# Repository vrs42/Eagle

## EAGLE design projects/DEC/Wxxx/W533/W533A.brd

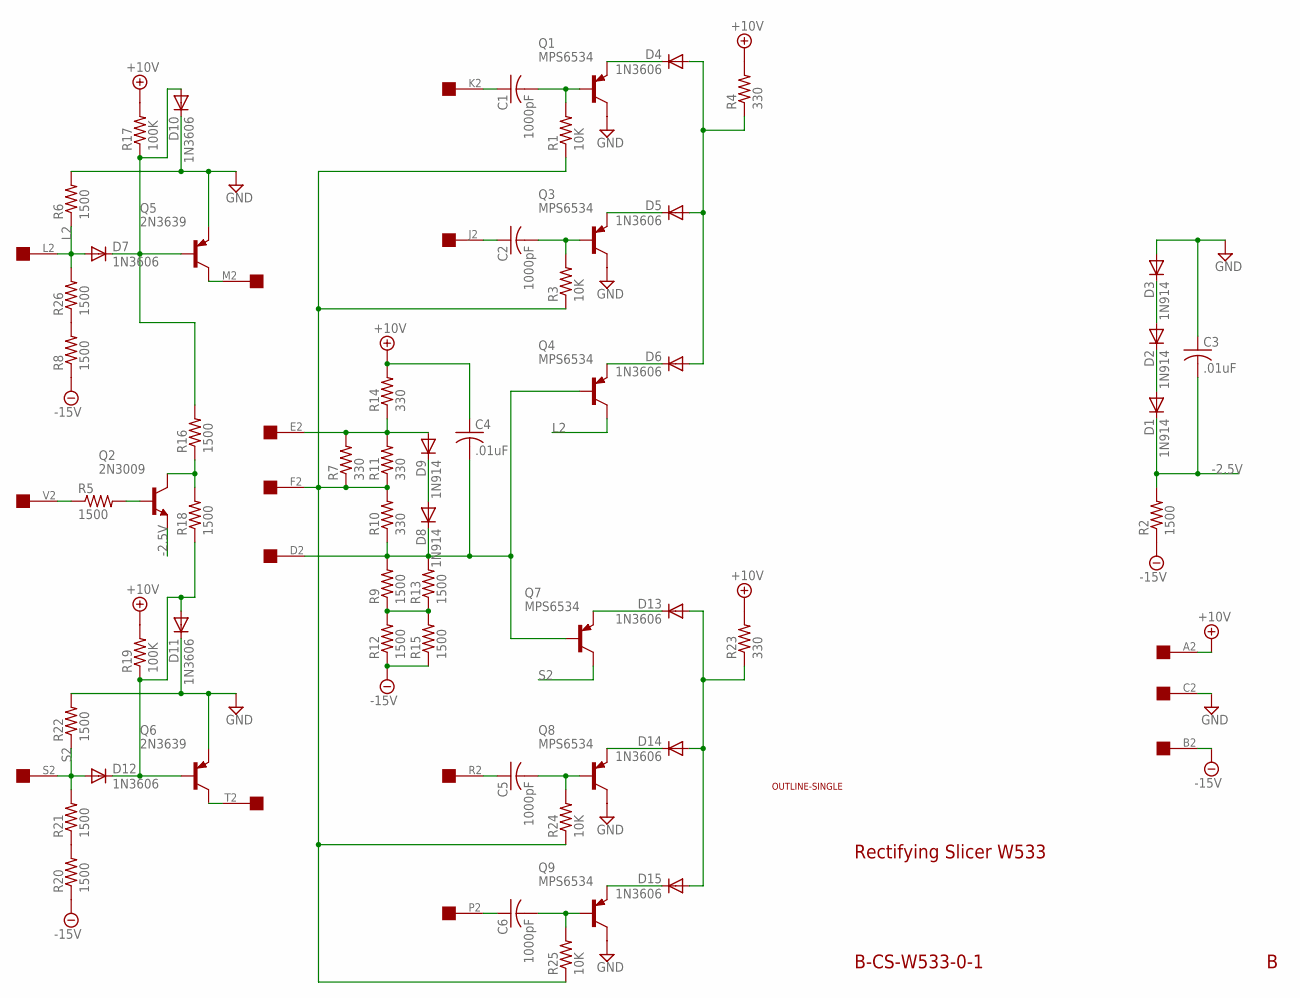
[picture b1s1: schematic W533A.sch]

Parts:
C1, C2, C5, C6: 1000pF; C075-032X103
C3, C4: .01uF; C050-025X075
D1, D2, D3, D8, D9: 1N914; DO35-10
D4, D5, D6, D7, D10, D11, D12, D13, D14, D15: 1N3606; DO35-10
Q1, Q3, Q4, Q7, Q8, Q9: MPS6534; TO39
Q2: 2N3009; TO5
Q5, Q6: 2N3639; TO39
R1, R3, R24, R25: 10K; 0207/10
R2, R5, R6, R8, R9, R12, R13, R15, R16, R18, R20, R21, R22, R26: 1500; 0207/10
R4, R7, R10, R11, R14, R23: 330; 0207/10
R17, R19: 100K; 0207/10
U$1: OUTLINE-SINGLE; SINGLE
U$2: EDGE-1; EDGE-CON1

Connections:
+10V: C4.1, R4.2, R14.2, R17.2, R19.2, R23.2, U$2.A2
-2.5V: C3.2, D1.C, Q2.1 (E), R2.2
-15V: R2.1, R8.1, R12.1, R15.1, R20.1, U$2.B2
GND: C3.1, D3.A, D10.C, D11.C, Q1.3 (C), Q3.3 (C), Q5.1 (E), Q6.1 (E), Q8.3 (C), Q9.3 (C), R6.2, R22.2, U$2.C2
L2: D7.A, Q4.3 (C), R6.1, R26.2, U$2.L2
unnamed: C1.1, U$2.K2
unnamed: R5.1, U$2.V2
unnamed: C1.2, Q1.2 (B), R1.2
unnamed: D4.C, Q1.1 (E)
unnamed: D5.C, Q3.1 (E)
unnamed: C2.1, U$2.J2
unnamed: D14.C, Q8.1 (E)
unnamed: C2.2, Q3.2 (B), R3.2
unnamed: D15.C, Q9.1 (E)
unnamed: Q2.2 (B), R5.2
unnamed: C5.1, U$2.R2
unnamed: Q6.3 (C), U$2.T2
unnamed: C5.2, Q8.2 (B), R24.2
unnamed: Q5.3 (C), U$2.M2
unnamed: R8.2, R26.1
unnamed: C6.1, U$2.P2
unnamed: D13.C, Q7.1 (E)
unnamed: C6.2, Q9.2 (B), R25.2
unnamed: R20.2, R21.1
unnamed: D6.C, Q4.1 (E)
unnamed: D7.C, D10.A, Q5.2 (B), R16.2, R17.1
unnamed: Q2.3 (C), R16.1, R18.2
unnamed: C4.2, D8.C, Q4.2 (B), Q7.2 (B), R9.2, R10.1, R13.2, U$2.D2
unnamed: D11.A, D12.C, Q6.2 (B), R18.1, R19.1
unnamed: R9.1, R12.2, R13.1, R15.2
unnamed: R1.1, R3.1, R7.1, R10.2, R11.1, R24.1, R25.1, U$2.F2
unnamed: D2.A, D3.C
unnamed: D4.A, D5.A, D6.A, R4.1
unnamed: D1.A, D2.C
unnamed: D8.A, D9.C
unnamed: D9.A, R7.2, R11.2, R14.1, U$2.E2
unnamed: D13.A, D14.A, D15.A, R23.1
S2: D12.A, Q7.3 (C), R21.2, R22.1, U$2.S2

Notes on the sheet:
Rectifying Slicer W533
B-CS-W533-0-1

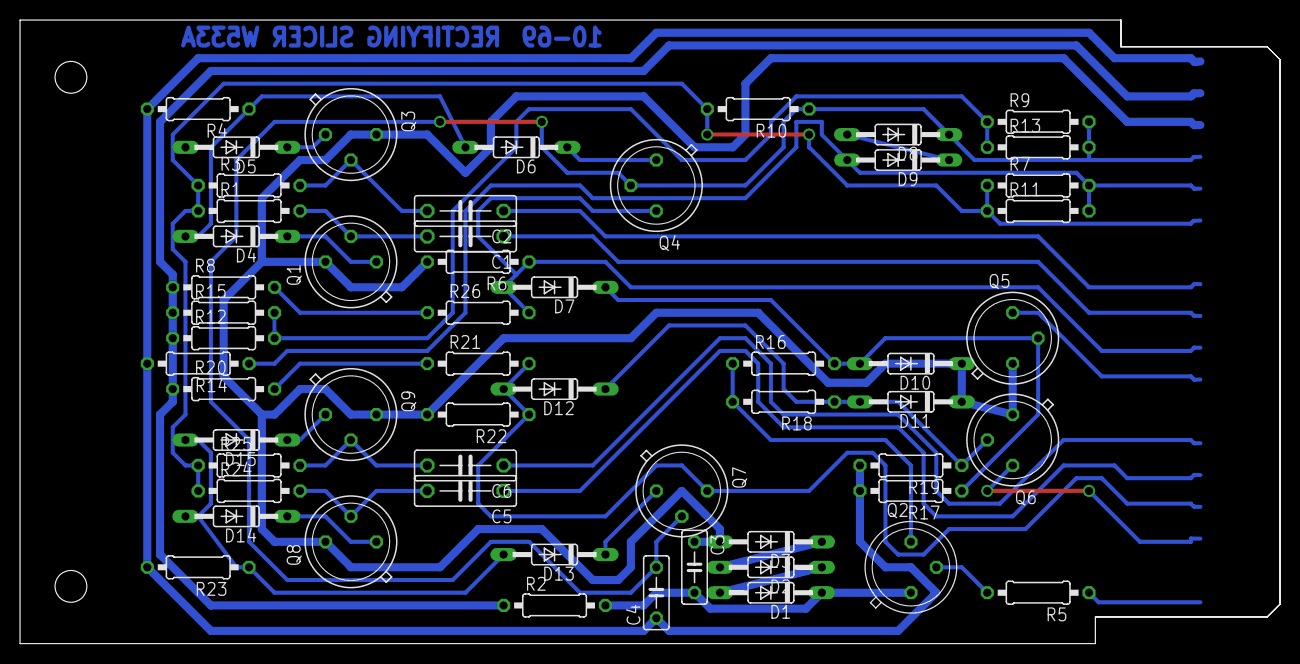
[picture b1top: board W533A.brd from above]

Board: 2 copper layers, 125.7 x 62.2 mm, 58 parts (0 on the bottom side), 38 nets.

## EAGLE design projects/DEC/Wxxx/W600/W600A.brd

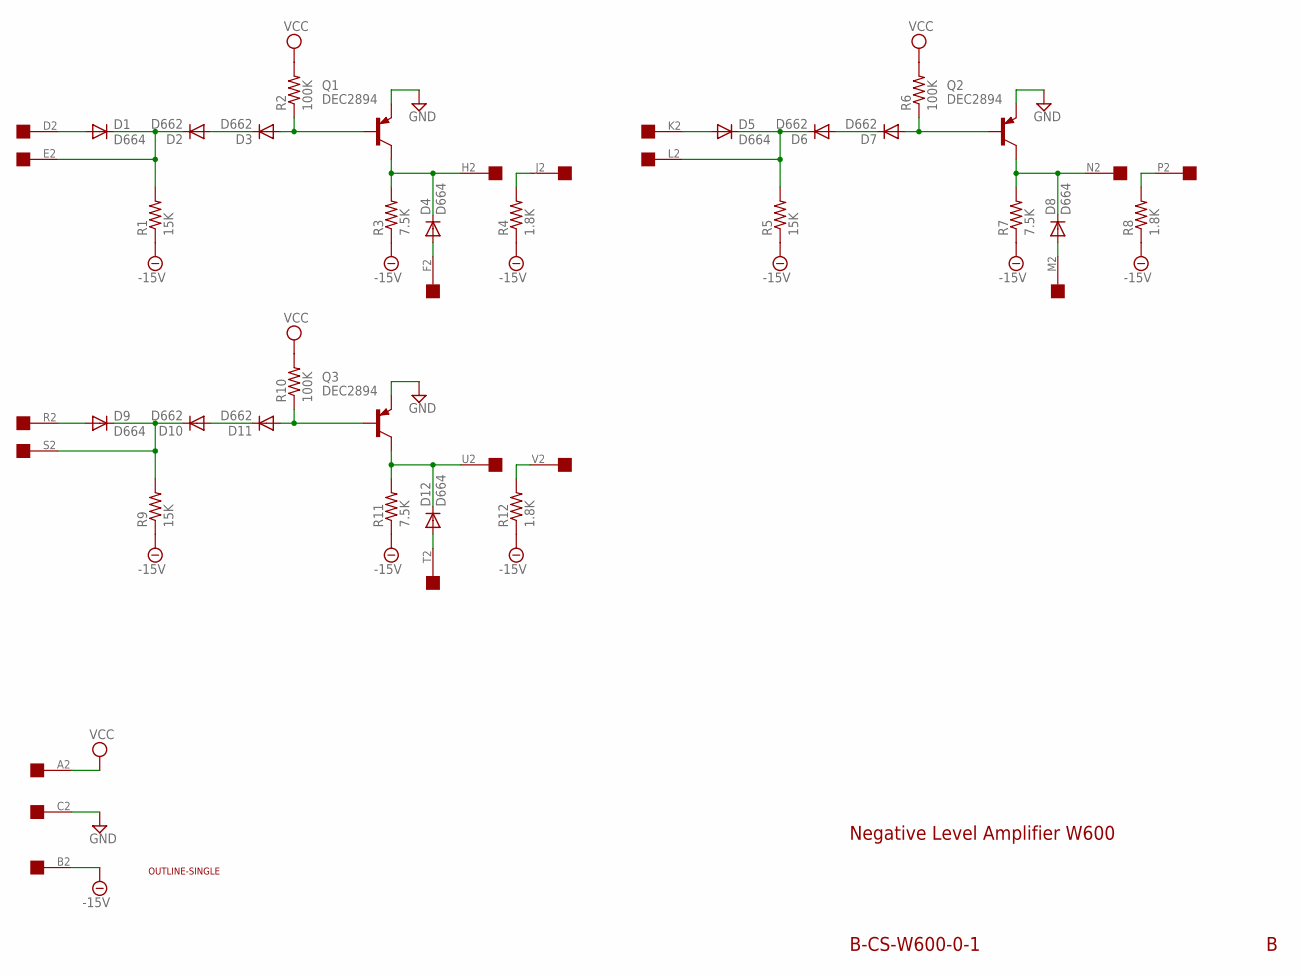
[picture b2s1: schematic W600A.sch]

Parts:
D1, D4, D5, D8, D9, D12: D664; DO35-10
D2, D3, D6, D7, D10, D11: D662; DO35-10
Q1, Q2, Q3: DEC2894; TO5
R1, R5, R9: 15K; 0207/10
R2, R6, R10: 100K; 0207/10
R3, R7, R11: 7.5K; 0207/10
R4, R8, R12: 1.8K; 0207/10
U$1: OUTLINE-SINGLE; SINGLE
U$2: EDGE-1; EDGE-CON1

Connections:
-15V: R1.1, R3.1, R4.1, R5.1, R7.1, R8.1, R9.1, R11.1, R12.1, U$2.B2
GND: Q1.1 (E), Q2.1 (E), Q3.1 (E), U$2.C2
unnamed: D3.A, Q1.2 (B), R2.1
unnamed: D2.A, D3.C
unnamed: D1.C, D2.C, R1.2, U$2.E2
unnamed: D1.A, U$2.D2
unnamed: D4.C, Q1.3 (C), R3.2, U$2.H2
unnamed: R4.2, U$2.J2
unnamed: D7.A, Q2.2 (B), R6.1
unnamed: D6.A, D7.C
unnamed: D5.C, D6.C, R5.2, U$2.L2
unnamed: D5.A, U$2.K2
unnamed: D8.C, Q2.3 (C), R7.2, U$2.N2
unnamed: R8.2, U$2.P2
unnamed: D11.A, Q3.2 (B), R10.1
unnamed: D10.A, D11.C
unnamed: D9.C, D10.C, R9.2, U$2.S2
unnamed: D9.A, U$2.R2
unnamed: D12.C, Q3.3 (C), R11.2, U$2.U2
unnamed: R12.2, U$2.V2
unnamed: D12.A, U$2.T2
unnamed: D4.A, U$2.F2
unnamed: D8.A, U$2.M2
VCC: R2.2, R6.2, R10.2, U$2.A2

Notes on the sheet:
Negative Level Amplifier W600
B-CS-W600-0-1

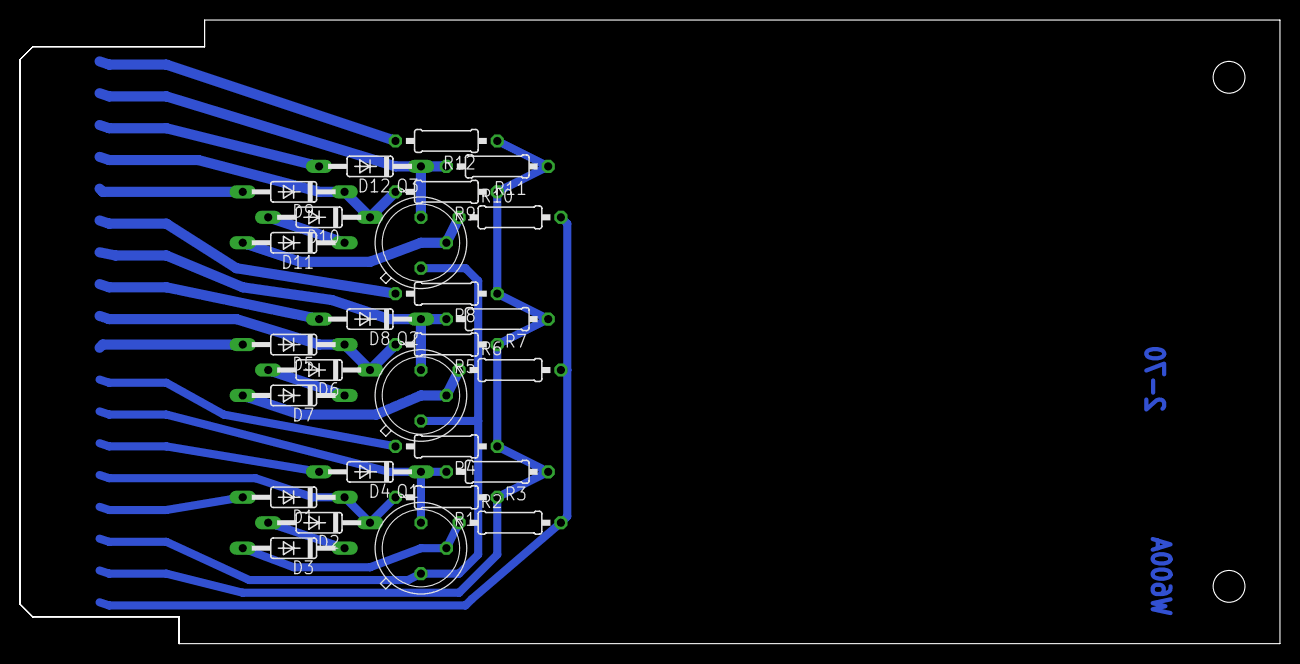
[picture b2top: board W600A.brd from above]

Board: 2 copper layers, 125.7 x 62.2 mm, 29 parts (0 on the bottom side), 24 nets.

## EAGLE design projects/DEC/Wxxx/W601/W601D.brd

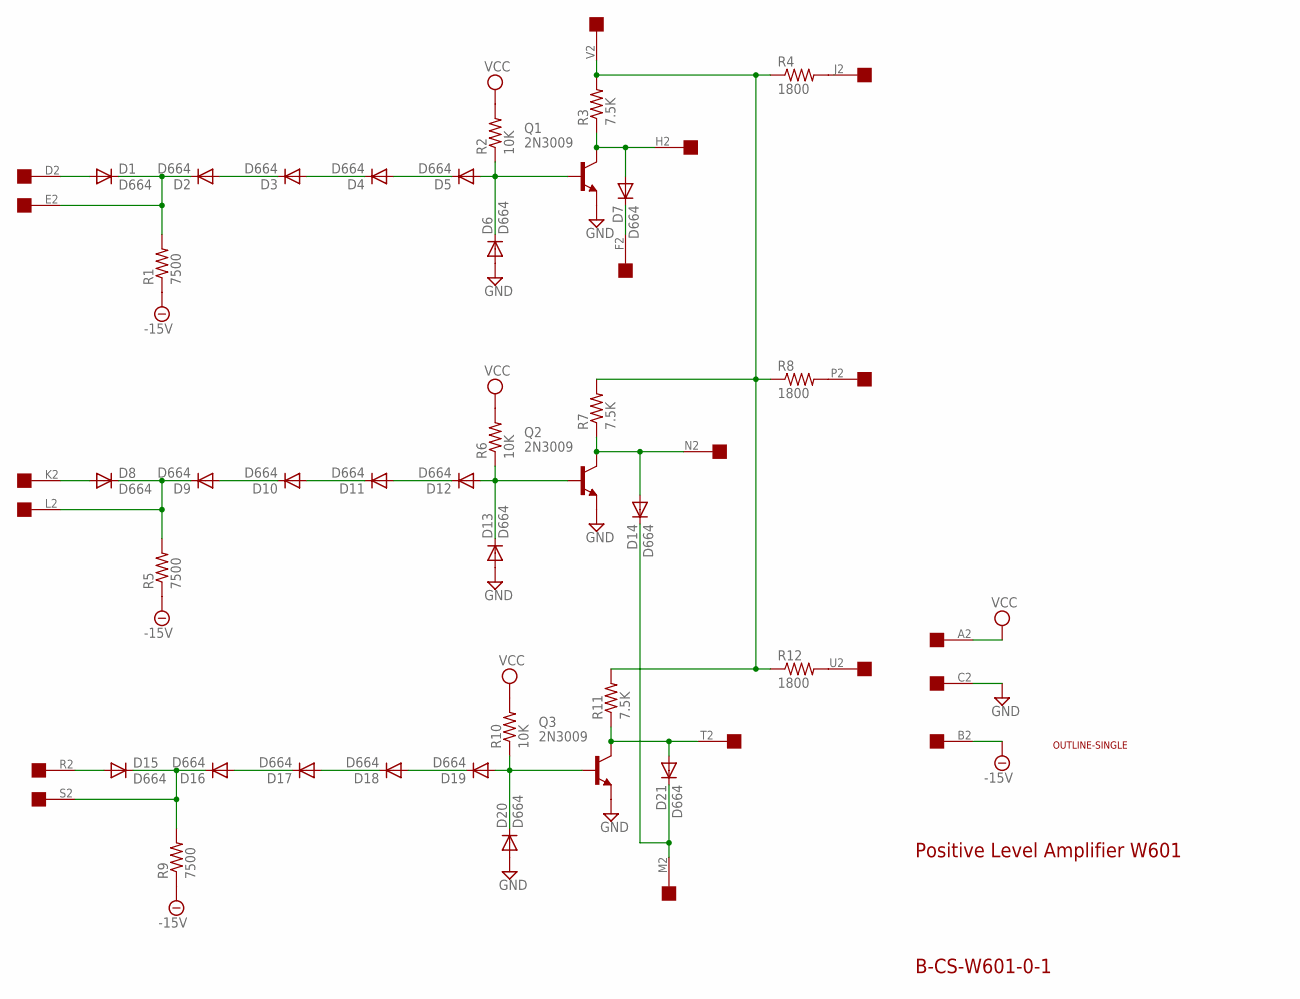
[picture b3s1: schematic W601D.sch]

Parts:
D1, D2, D3, D4, D5, D6, D7, D8, D9, D10, D11, D12, D13, D14, D15, D16, D17, D18, D19, D20, D21: D664; DO35-10
Q1, Q2, Q3: 2N3009; TO5
R1, R5, R9: 7500; 0207/10
R2, R6, R10: 10K; 0207/10
R3, R7, R11: 7.5K; 0207/10
R4, R8, R12: 1800; 0207/10
U$1: OUTLINE-SINGLE; SINGLE
U$2: EDGE-1; EDGE-CON1

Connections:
-15V: R1.1, R5.1, R9.1, U$2.B2
GND: D6.A, D13.A, D20.A, Q1.1 (E), Q2.1 (E), Q3.1 (E), U$2.C2
unnamed: D5.A, D6.C, Q1.2 (B), R2.1
unnamed: D4.A, D5.C
unnamed: D1.C, D2.C, R1.2, U$2.E2
unnamed: D1.A, U$2.D2
unnamed: D7.A, Q1.3 (C), R3.1, U$2.H2
unnamed: R4.2, U$2.J2
unnamed: D12.A, D13.C, Q2.2 (B), R6.1
unnamed: D11.A, D12.C
unnamed: D8.C, D9.C, R5.2, U$2.L2
unnamed: D8.A, U$2.K2
unnamed: D14.C, D21.C, U$2.M2
unnamed: R8.2, U$2.P2
unnamed: D19.A, D20.C, Q3.2 (B), R10.1
unnamed: D18.A, D19.C
unnamed: D15.C, D16.C, R9.2, U$2.S2
unnamed: D15.A, U$2.R2
unnamed: D7.C, U$2.F2
unnamed: R12.2, U$2.U2
unnamed: R3.2, R4.1, R7.2, R8.1, R11.2, R12.1, U$2.V2
unnamed: D16.A, D17.C
unnamed: D17.A, D18.C
unnamed: D9.A, D10.C
unnamed: D10.A, D11.C
unnamed: D2.A, D3.C
unnamed: D14.A, Q2.3 (C), R7.1, U$2.N2
unnamed: D21.A, Q3.3 (C), R11.1, U$2.T2
unnamed: D3.A, D4.C
VCC: R2.2, R6.2, R10.2, U$2.A2

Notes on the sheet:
Positive Level Amplifier W601
B-CS-W601-0-1

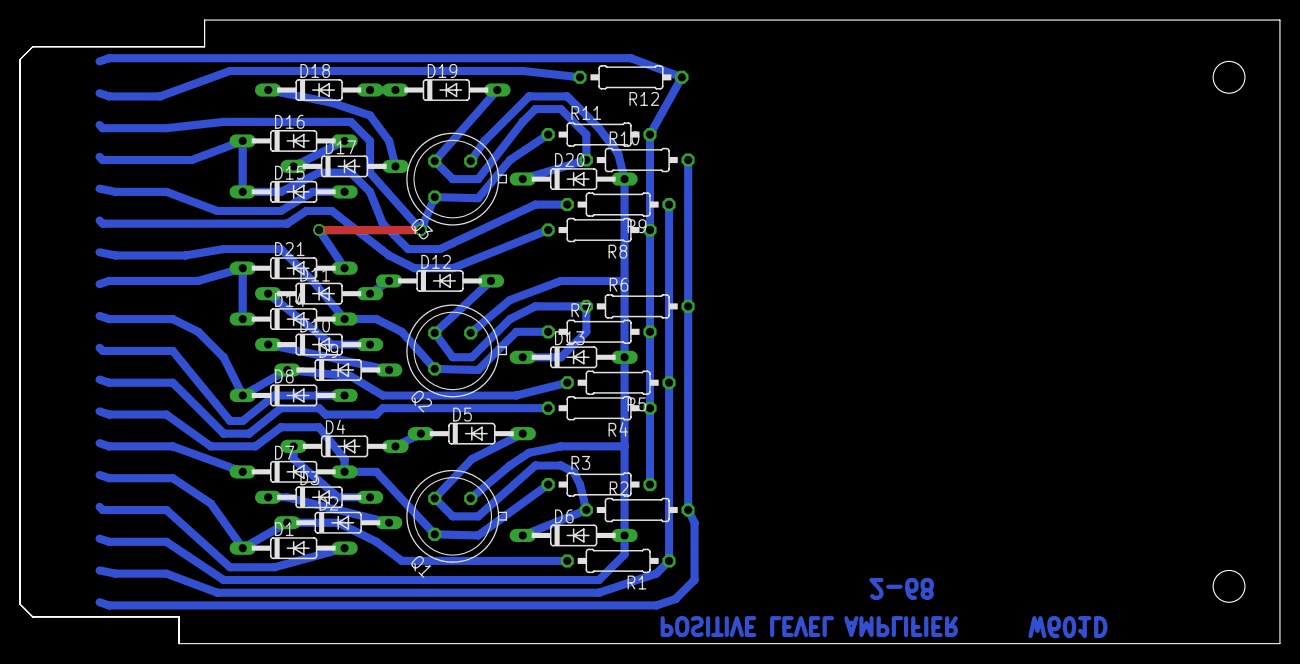
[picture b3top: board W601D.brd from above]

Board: 2 copper layers, 125.7 x 62.2 mm, 38 parts (0 on the bottom side), 30 nets.

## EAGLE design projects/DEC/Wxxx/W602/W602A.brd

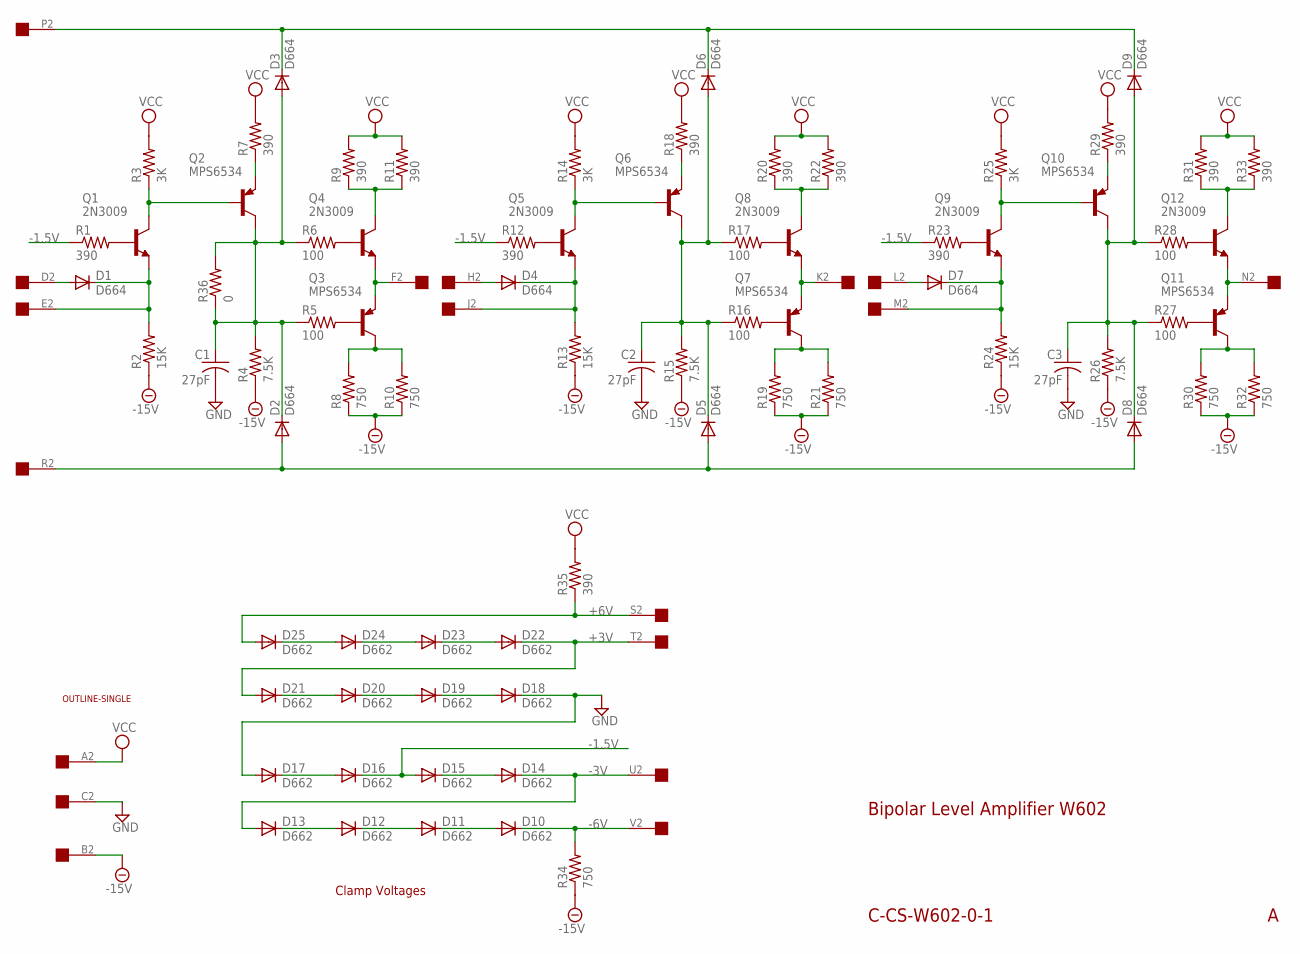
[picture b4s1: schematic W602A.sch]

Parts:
C1, C2, C3: 27pF; C063-025X075
D1, D2, D3, D4, D5, D6, D7, D8, D9: D664; DO35-10
D10, D11, D12, D13, D14, D15, D16, D17, D18, D19, D20, D21, D22, D23, D24, D25: D662; DO35-10
Q1, Q4, Q5, Q8, Q9, Q12: 2N3009; TO5
Q2, Q3, Q6, Q7, Q10, Q11: MPS6534; TO5
R1, R7, R9, R11, R12, R18, R20, R22, R23, R29, R31, R33, R35: 390; 0207/10
R2, R13, R24: 15K; 0207/10
R3, R14, R25: 3K; 0207/10
R4, R15, R26: 7.5K; 0207/10
R5, R6, R16, R17, R27, R28: 100; 0207/10
R8, R10, R19, R21, R30, R32, R34: 750; 0207/10
R36: 0; 0207/10
U$1: OUTLINE-SINGLE; SINGLE
U$2: EDGE-1; EDGE-CON1

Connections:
+3V: D21.A, D22.C, U$2.T2
+6V: D25.A, R35.1, U$2.S2
-1.5V: D15.A, D16.C, R1.1, R12.1, R23.1
-3V: D13.A, D14.C, U$2.U2
-6V: D10.C, R34.2, U$2.V2
-15V: R2.1, R4.1, R8.1, R10.1, R13.1, R15.1, R19.1, R21.1, R24.1, R26.1, R30.1, R32.1, R34.1, U$2.B2
GND: C1.2, C2.2, C3.2, D17.A, D18.C, U$2.C2
unnamed: Q1.3 (C), Q2.2 (B), R3.1
unnamed: Q2.1 (E), R7.1
unnamed: C1.1, D2.C, D3.A, Q2.3 (C), R4.2, R5.1, R6.1, R36.1, R36.2
unnamed: Q1.2 (B), R1.2
unnamed: D1.C, Q1.1 (E), R2.2, U$2.E2
unnamed: D1.A, U$2.D2
unnamed: Q3.3 (C), R8.2, R10.2
unnamed: Q3.2 (B), R5.2
unnamed: Q5.3 (C), Q6.2 (B), R14.1
unnamed: Q4.2 (B), R6.2
unnamed: Q3.1 (E), Q4.1 (E), U$2.F2
unnamed: Q4.3 (C), R9.1, R11.1
unnamed: Q6.1 (E), R18.1
unnamed: C2.1, D5.C, D6.A, Q6.3 (C), R15.2, R16.1, R17.1
unnamed: Q5.2 (B), R12.2
unnamed: D4.C, Q5.1 (E), R13.2, U$2.J2
unnamed: D4.A, U$2.H2
unnamed: Q7.3 (C), R19.2, R21.2
unnamed: Q7.2 (B), R16.2
unnamed: Q8.2 (B), R17.2
unnamed: Q7.1 (E), Q8.1 (E), U$2.K2
unnamed: Q8.3 (C), R20.1, R22.1
unnamed: Q9.3 (C), Q10.2 (B), R25.1
unnamed: Q10.1 (E), R29.1
unnamed: C3.1, D8.C, D9.A, Q10.3 (C), R26.2, R27.1, R28.1
unnamed: Q9.2 (B), R23.2
unnamed: D7.C, Q9.1 (E), R24.2, U$2.M2
unnamed: D7.A, U$2.L2
unnamed: Q11.3 (C), R30.2, R32.2
unnamed: Q11.2 (B), R27.2
unnamed: Q12.2 (B), R28.2
unnamed: Q11.1 (E), Q12.1 (E), U$2.N2
unnamed: Q12.3 (C), R31.1, R33.1
unnamed: D2.A, D5.A, D8.A, U$2.R2
unnamed: D3.C, D6.C, D9.C, U$2.P2
unnamed: D10.A, D11.C
unnamed: D11.A, D12.C
unnamed: D12.A, D13.C
unnamed: D14.A, D15.C
unnamed: D16.A, D17.C
unnamed: D18.A, D19.C
unnamed: D19.A, D20.C
unnamed: D20.A, D21.C
unnamed: D22.A, D23.C
unnamed: D23.A, D24.C
unnamed: D24.A, D25.C
VCC: R3.2, R7.2, R9.2, R11.2, R14.2, R18.2, R20.2, R22.2, R25.2, R29.2, R31.2, R33.2, R35.2, U$2.A2

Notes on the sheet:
Clamp Voltages
Bipolar Level Amplifier W602
C-CS-W602-0-1

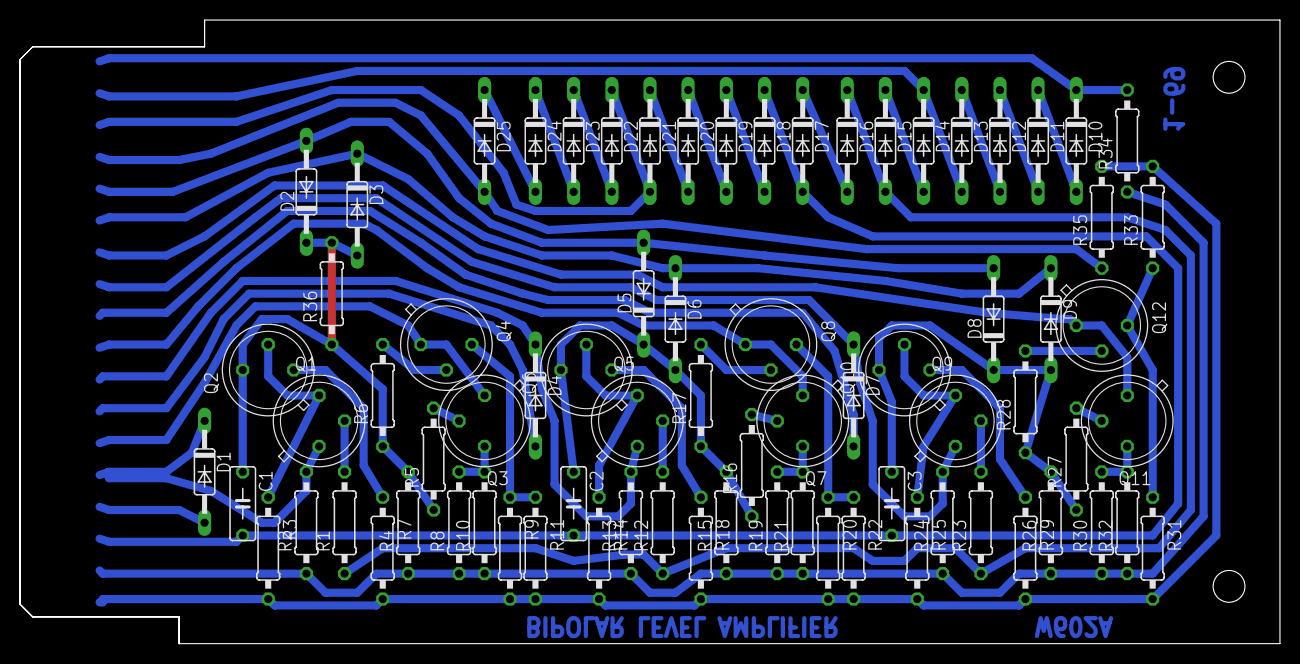
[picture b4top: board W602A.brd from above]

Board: 2 copper layers, 125.7 x 62.2 mm, 78 parts (0 on the bottom side), 54 nets.
